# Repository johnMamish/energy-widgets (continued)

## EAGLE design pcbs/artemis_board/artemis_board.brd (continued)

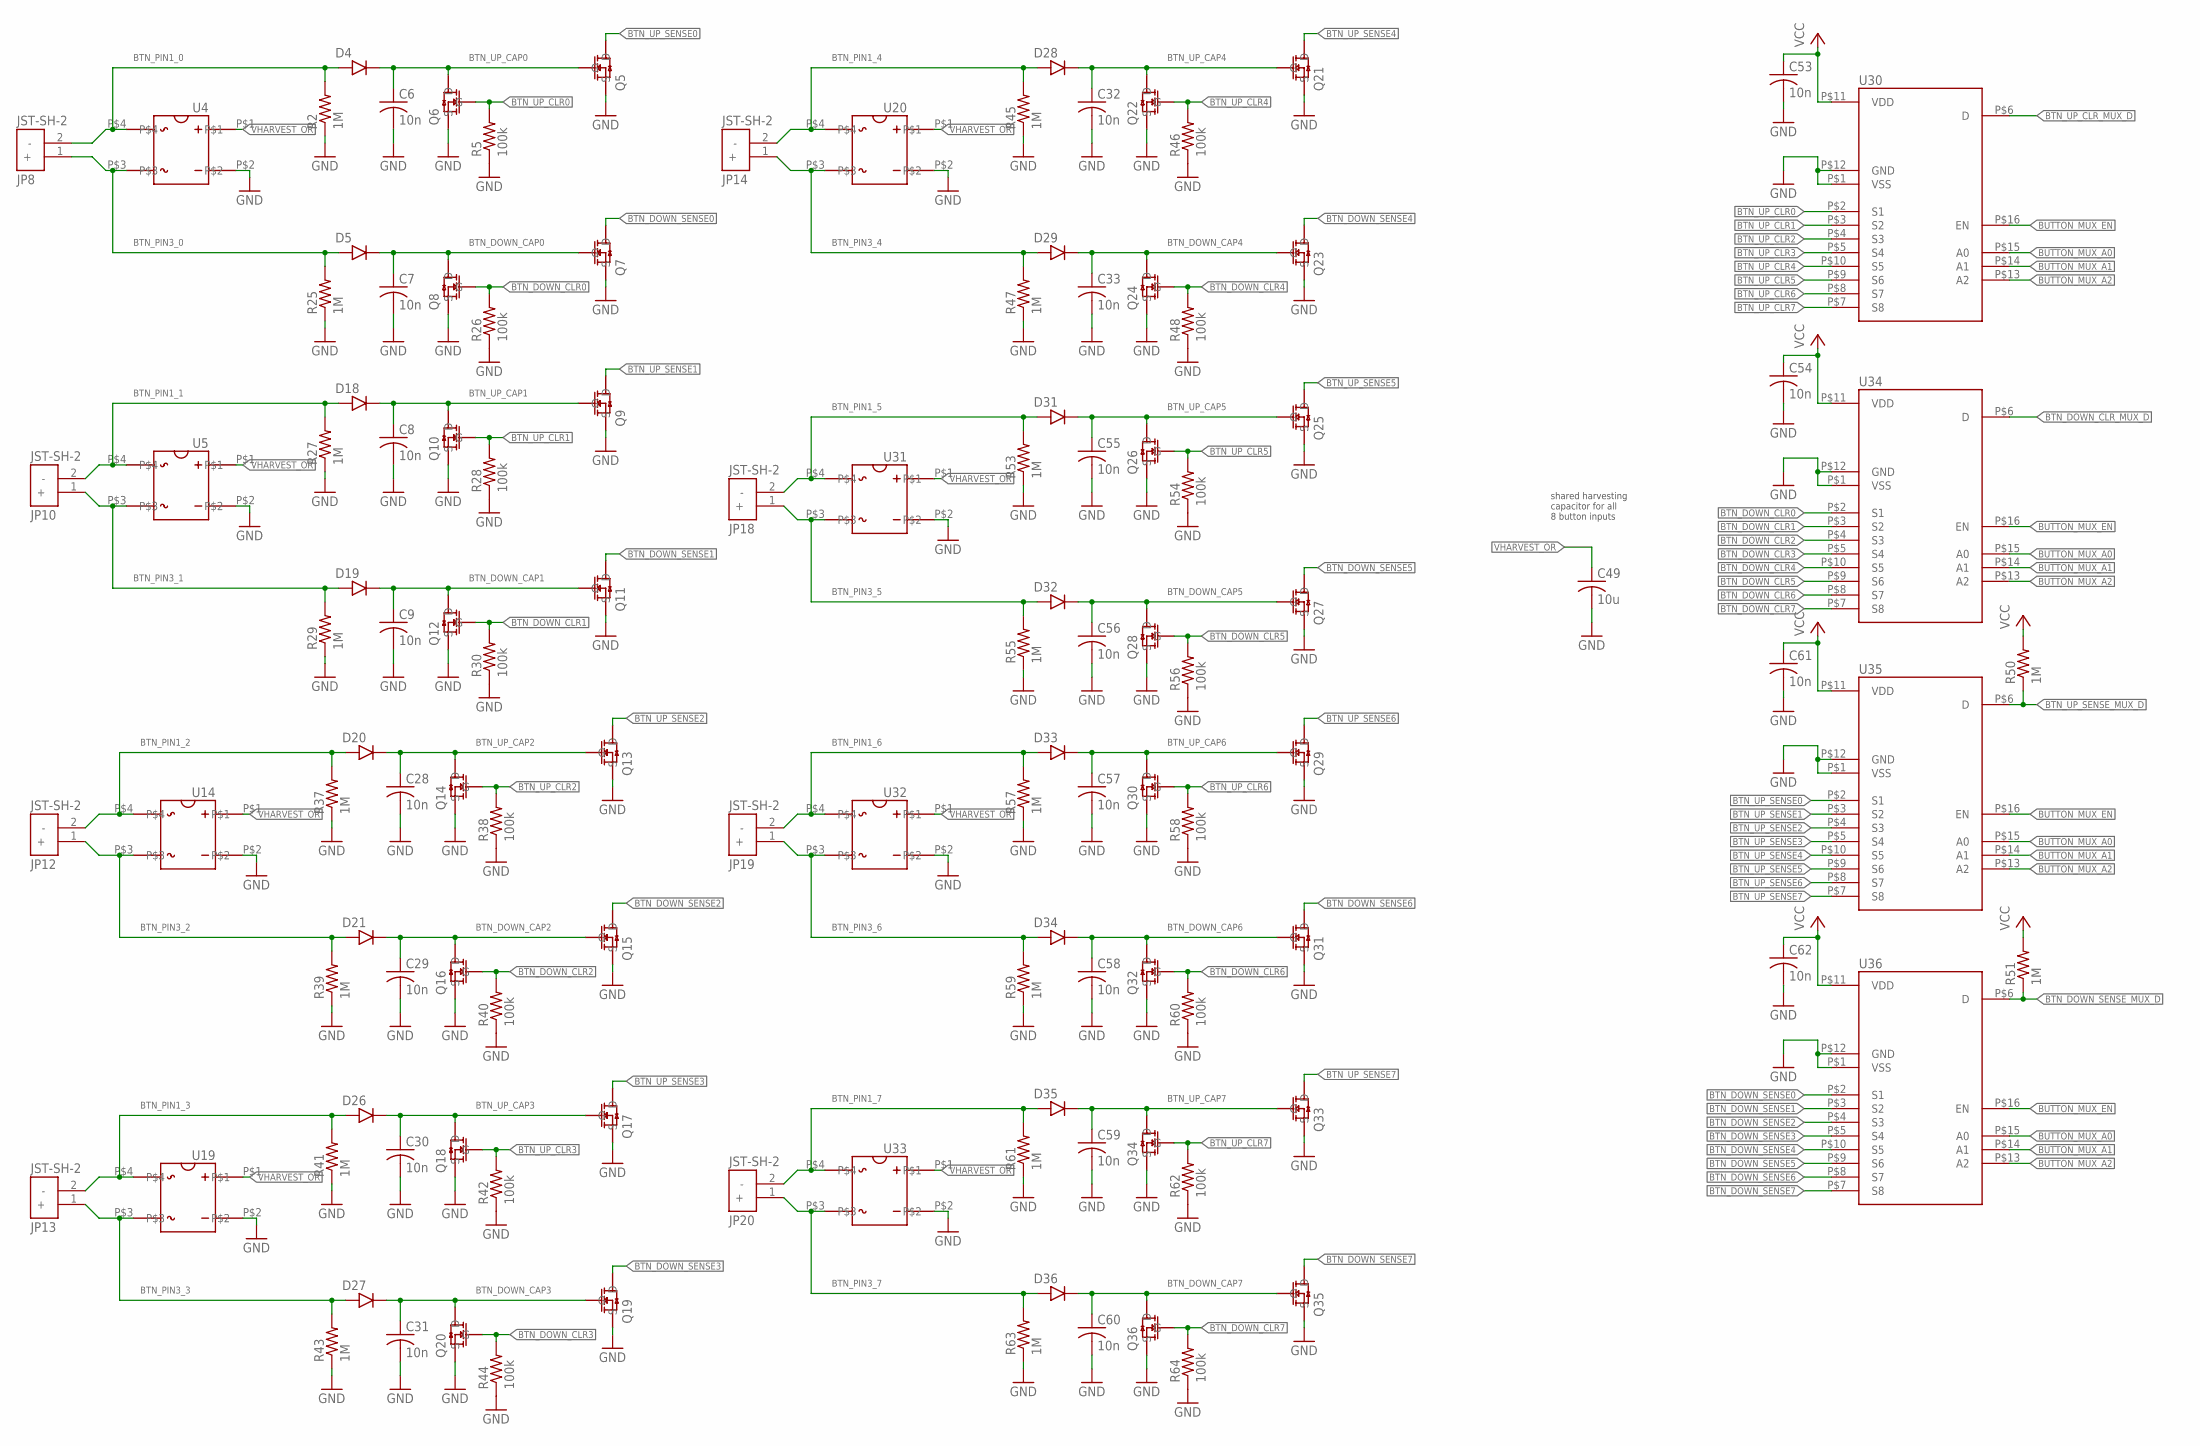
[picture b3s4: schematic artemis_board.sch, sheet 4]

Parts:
C6, C7, C8, C9, C28, C29, C30, C31, C32, C33, C53, C54, C55, C56, C57, C58, C59, C60, C61, C62: 10n; C0402; MFR_PN CL05B103KO5NNNC
C49: 10u; C0603; MFR_PN CL10A106MQ8NNNC
D4, D5, D18, D19, D20, D21, D26, D27, D28, D29, D31, D32, D33, D34, D35, D36: DFLU1200; MFR_PN DFLU1200-7
JP8, JP10, JP12, JP13, JP14, JP18, JP19, JP20: JST-SH-2; MFR_PN SM02B-SRSS-TB(LF)(SN)
Q5, Q7, Q9, Q11, Q13, Q15, Q17, Q19, Q21, Q23, Q25, Q27, Q29, Q31, Q33, Q35: 2N7002K-7
Q6, Q8, Q10, Q12, Q14, Q16, Q18, Q20, Q22, Q24, Q26, Q28, Q30, Q32, Q34, Q36: BSS138K
R2, R25, R27, R29, R37, R39, R41, R43, R45, R47, R50, R51, R53, R55, R57, R59, R61, R63: 1M; R0402; MFR_PN RC0402FR-071ML
R5, R26, R28, R30, R38, R40, R42, R44, R46, R48, R54, R56, R58, R60, R62, R64: 100k; R0402; MFR_PN RC0402FR-07100KL
U4, U5, U14, U19, U20, U31, U32, U33: CDBHD140L-G; CDBHDXX0L-G; MFR_PN CDBHD140L-G
U30, U34, U35, U36: TMUX1108RSVR; UQFN16-RSV0016A

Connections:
BTN_DOWN_CAP0: C7.1, D5.K, Q7.G, Q8.D
BTN_DOWN_CAP1: C9.1, D19.K, Q11.G, Q12.D
BTN_DOWN_CAP2: C29.1, D21.K, Q15.G, Q16.D
BTN_DOWN_CAP3: C31.1, D27.K, Q19.G, Q20.D
BTN_DOWN_CAP4: C33.1, D29.K, Q23.G, Q24.D
BTN_DOWN_CAP5: C56.1, D32.K, Q27.G, Q28.D
BTN_DOWN_CAP6: C58.1, D34.K, Q31.G, Q32.D
BTN_DOWN_CAP7: C60.1, D36.K, Q35.G, Q36.D
BTN_DOWN_CLR0: Q8.G, R26.2, U34.P$2 (S1)
BTN_DOWN_CLR1: Q12.G, R30.2, U34.P$3 (S2)
BTN_DOWN_CLR2: Q16.G, R40.2, U34.P$4 (S3)
BTN_DOWN_CLR3: Q20.G, R44.2, U34.P$5 (S4)
BTN_DOWN_CLR4: Q24.G, R48.2, U34.P$10 (S5)
BTN_DOWN_CLR5: Q28.G, R56.2, U34.P$9 (S6)
BTN_DOWN_CLR6: Q32.G, R60.2, U34.P$8 (S7)
BTN_DOWN_CLR7: Q36.G, R64.2, U34.P$7 (S8)
BTN_DOWN_CLR_MUX_D: U34.P$6 (D); also elsewhere on the board
BTN_DOWN_SENSE0: Q7.D, U36.P$2 (S1)
BTN_DOWN_SENSE1: Q11.D, U36.P$3 (S2)
BTN_DOWN_SENSE2: Q15.D, U36.P$4 (S3)
BTN_DOWN_SENSE3: Q19.D, U36.P$5 (S4)
BTN_DOWN_SENSE4: Q23.D, U36.P$10 (S5)
BTN_DOWN_SENSE5: Q27.D, U36.P$9 (S6)
BTN_DOWN_SENSE6: Q31.D, U36.P$8 (S7)
BTN_DOWN_SENSE7: Q35.D, U36.P$7 (S8)
BTN_DOWN_SENSE_MUX_D: R51.1, U36.P$6 (D); also elsewhere on the board
BTN_PIN1_0: D4.A, JP8.2 (-), R2.2, U4.P$4
BTN_PIN1_1: D18.A, JP10.2 (-), R27.2, U5.P$4
BTN_PIN1_2: D20.A, JP12.2 (-), R37.2, U14.P$4
BTN_PIN1_3: D26.A, JP13.2 (-), R41.2, U19.P$4
BTN_PIN1_4: D28.A, JP14.2 (-), R45.2, U20.P$4
BTN_PIN1_5: D31.A, JP18.2 (-), R53.2, U31.P$4
BTN_PIN1_6: D33.A, JP19.2 (-), R57.2, U32.P$4
BTN_PIN1_7: D35.A, JP20.2 (-), R61.2, U33.P$4
BTN_PIN3_0: D5.A, JP8.1 (+), R25.2, U4.P$3
BTN_PIN3_1: D19.A, JP10.1 (+), R29.2, U5.P$3
BTN_PIN3_2: D21.A, JP12.1 (+), R39.2, U14.P$3
BTN_PIN3_3: D27.A, JP13.1 (+), R43.2, U19.P$3
BTN_PIN3_4: D29.A, JP14.1 (+), R47.2, U20.P$3
BTN_PIN3_5: D32.A, JP18.1 (+), R55.2, U31.P$3
BTN_PIN3_6: D34.A, JP19.1 (+), R59.2, U32.P$3
BTN_PIN3_7: D36.A, JP20.1 (+), R63.2, U33.P$3
BTN_UP_CAP0: C6.1, D4.K, Q5.G, Q6.D
BTN_UP_CAP1: C8.1, D18.K, Q9.G, Q10.D
BTN_UP_CAP2: C28.1, D20.K, Q13.G, Q14.D
BTN_UP_CAP3: C30.1, D26.K, Q17.G, Q18.D
BTN_UP_CAP4: C32.1, D28.K, Q21.G, Q22.D
BTN_UP_CAP5: C55.1, D31.K, Q25.G, Q26.D
BTN_UP_CAP6: C57.1, D33.K, Q29.G, Q30.D
BTN_UP_CAP7: C59.1, D35.K, Q33.G, Q34.D
BTN_UP_CLR0: Q6.G, R5.2, U30.P$2 (S1)
BTN_UP_CLR1: Q10.G, R28.2, U30.P$3 (S2)
BTN_UP_CLR2: Q14.G, R38.2, U30.P$4 (S3)
BTN_UP_CLR3: Q18.G, R42.2, U30.P$5 (S4)
BTN_UP_CLR4: Q22.G, R46.2, U30.P$10 (S5)
BTN_UP_CLR5: Q26.G, R54.2, U30.P$9 (S6)
BTN_UP_CLR6: Q30.G, R58.2, U30.P$8 (S7)
BTN_UP_CLR7: Q34.G, R62.2, U30.P$7 (S8)
BTN_UP_CLR_MUX_D: U30.P$6 (D); also elsewhere on the board
BTN_UP_SENSE0: Q5.D, U35.P$2 (S1)
BTN_UP_SENSE1: Q9.D, U35.P$3 (S2)
BTN_UP_SENSE2: Q13.D, U35.P$4 (S3)
BTN_UP_SENSE3: Q17.D, U35.P$5 (S4)
BTN_UP_SENSE4: Q21.D, U35.P$10 (S5)
BTN_UP_SENSE5: Q25.D, U35.P$9 (S6)
BTN_UP_SENSE6: Q29.D, U35.P$8 (S7)
BTN_UP_SENSE7: Q33.D, U35.P$7 (S8)
BTN_UP_SENSE_MUX_D: R50.1, U35.P$6 (D); also elsewhere on the board
BUTTON_MUX_A0: U30.P$15 (A0), U34.P$15 (A0), U35.P$15 (A0), U36.P$15 (A0); also elsewhere on the board
BUTTON_MUX_A1: U30.P$14 (A1), U34.P$14 (A1), U35.P$14 (A1), U36.P$14 (A1); also elsewhere on the board
BUTTON_MUX_A2: U30.P$13 (A2), U34.P$13 (A2), U35.P$13 (A2), U36.P$13 (A2); also elsewhere on the board
BUTTON_MUX_EN: U30.P$16 (EN), U34.P$16 (EN), U35.P$16 (EN), U36.P$16 (EN); also elsewhere on the board
GND: C6.2, C7.2, C8.2, C9.2, C28.2, C29.2, C30.2, C31.2, C32.2, C33.2, C49.2, C53.2, C54.2, C55.2, C56.2, C57.2, C58.2, C59.2, C60.2, C61.2, C62.2, Q5.S, Q6.S, Q7.S, Q8.S, Q9.S, Q10.S, Q11.S, Q12.S, Q13.S, Q14.S, Q15.S, Q16.S, Q17.S, Q18.S, Q19.S, Q20.S, Q21.S, Q22.S, Q23.S, Q24.S, Q25.S, Q26.S, Q27.S, Q28.S, Q29.S, Q30.S, Q31.S, Q32.S, Q33.S, Q34.S, Q35.S, Q36.S, R2.1, R5.1, R25.1, R26.1, R27.1, R28.1, R29.1, R30.1, R37.1, R38.1, R39.1, R40.1, R41.1, R42.1, R43.1, R44.1, R45.1, R46.1, R47.1, R48.1, R53.1, R54.1, R55.1, R56.1, R57.1, R58.1, R59.1, R60.1, R61.1, R62.1, R63.1, R64.1, U4.P$2, U5.P$2, U14.P$2, U19.P$2, U20.P$2, U30.P$1 (VSS), U30.P$12 (GND), U31.P$2, U32.P$2, U33.P$2, U34.P$1 (VSS), U34.P$12 (GND), U35.P$1 (VSS), U35.P$12 (GND), U36.P$1 (VSS), U36.P$12 (GND); also elsewhere on the board
VCC: C53.1, C54.1, C61.1, C62.1, R50.2, R51.2, U30.P$11 (VDD), U34.P$11 (VDD), U35.P$11 (VDD), U36.P$11 (VDD); also elsewhere on the board
VHARVEST_OR: C49.1, U4.P$1, U5.P$1, U14.P$1, U19.P$1, U20.P$1, U31.P$1, U32.P$1, U33.P$1; also elsewhere on the board

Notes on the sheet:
shared harvesting capacitor for all 8 button inputs

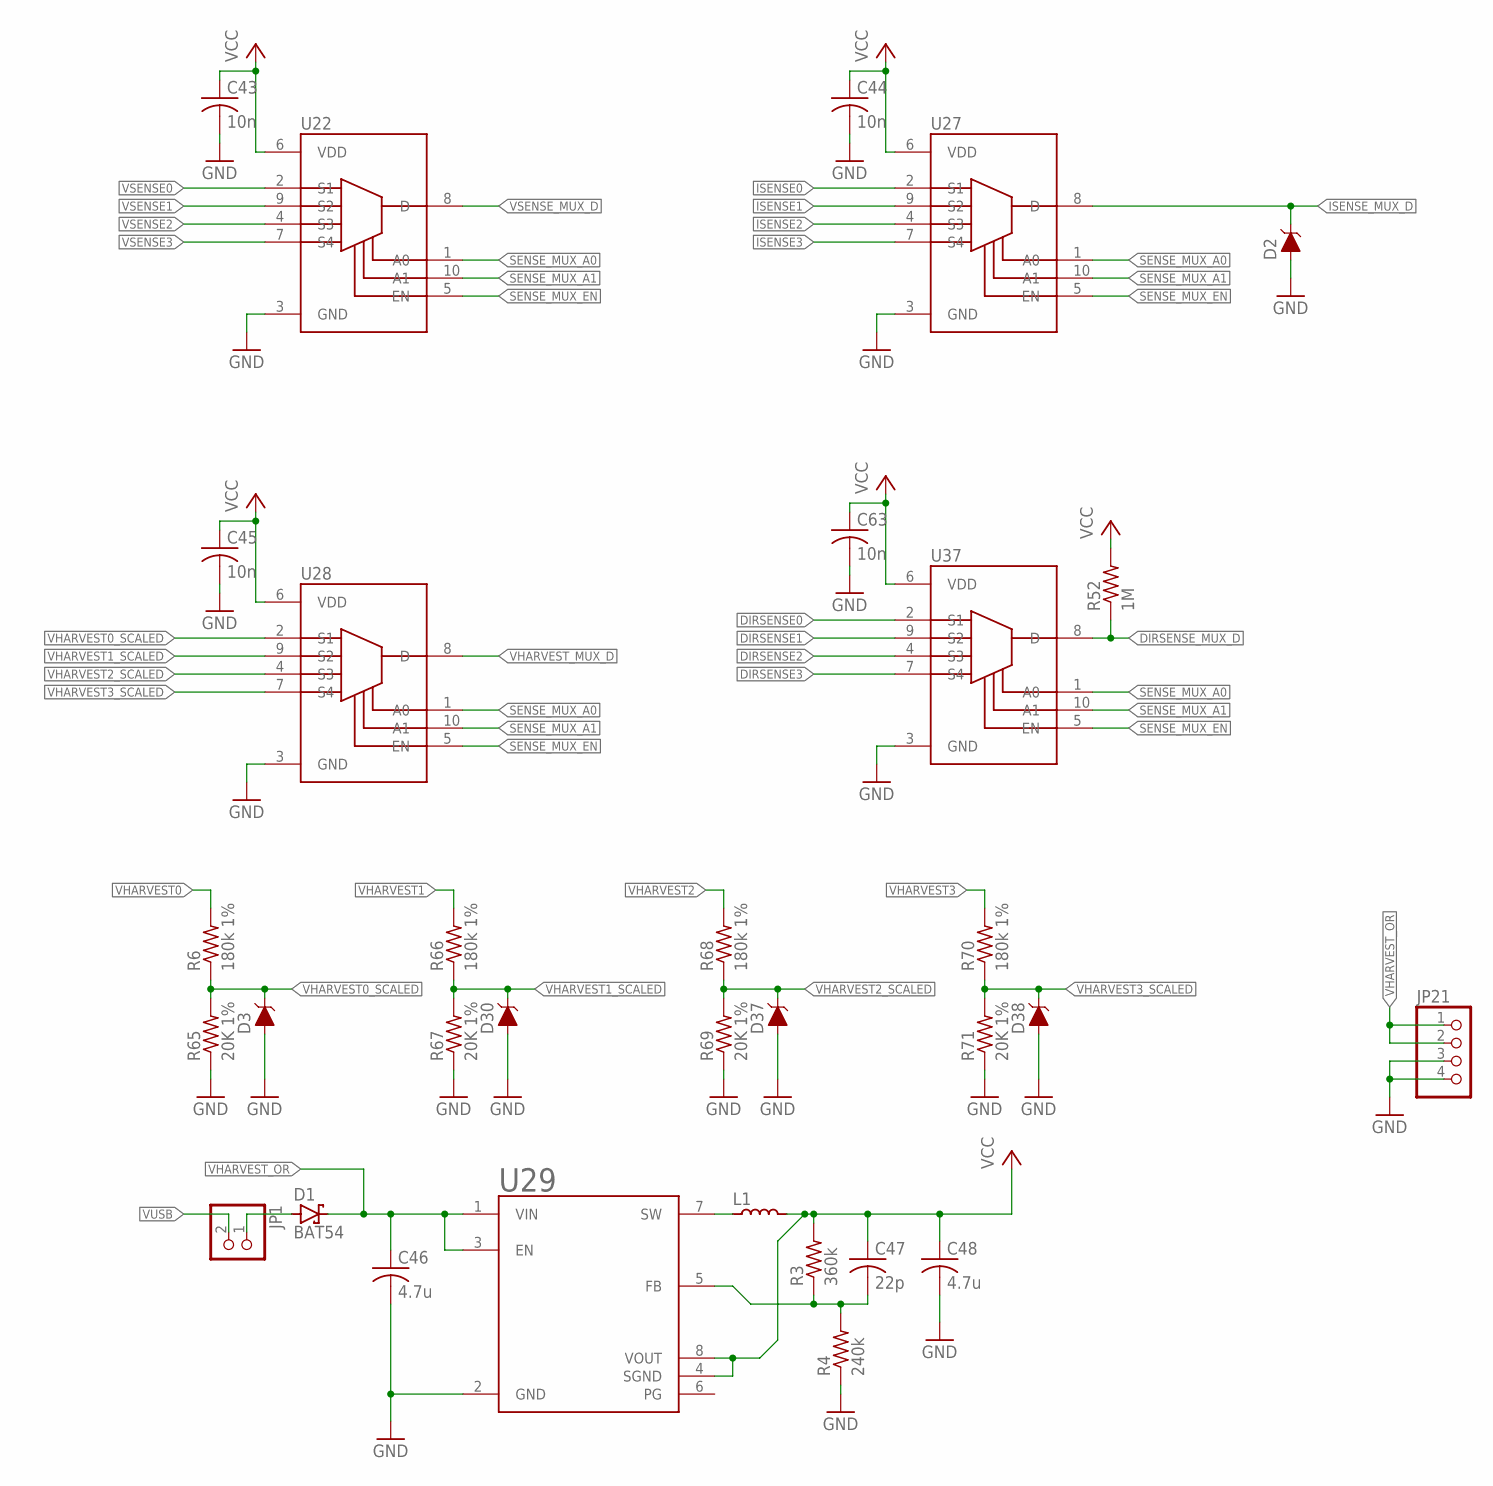
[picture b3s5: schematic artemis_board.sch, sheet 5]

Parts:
C43, C44, C45, C63: 10n; C0402; MFR_PN CL05B103KO5NNNC
C46, C48: 4.7u; C0603; MFR_PN CL10A475KA8NQNC
C47: 22p; C0402; MFR_PN C0603C220J5GACTU
D1: BAT54; SOT23; MFR_PN BAT54
D2, D3, D30, D37, D38: 3.3V; SOD-323; MFR_PN BZT52C2V0S-7-F
JP1: PINHD-1X2; 1X02
JP21: PINHD-1X4; 1X04
L1: 22u; LQH3NPNXXXXMEX; MFR_PN LQH3NPN220MJRL
R3: 360k; R0603; MFR_PN ERJ-3GEYJ364V
R4: 240k; R0603; MFR_PN ERJ-3GEYJ244V
R6, R66, R68, R70: 180k 1%; R0402; MFR_PN ERJ-2RKF1803X
R52: 1M; R0402; MFR_PN RC0402FR-071ML
R65, R67, R69, R71: 20K 1%; R0402; MFR_PN ERJ-2RKF2002X
U22, U27, U28, U37: TMUX1104DGSR; SOP50P490X110-10N
U29: TPS62120; SOP65P280X145-8N; MFR_PN TPS62120

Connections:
DIRSENSE0: U37.2 (S1); also elsewhere on the board
DIRSENSE1: U37.9 (S2); also elsewhere on the board
DIRSENSE2: U37.4 (S3); also elsewhere on the board
DIRSENSE3: U37.7 (S4); also elsewhere on the board
DIRSENSE_MUX_D: R52.1, U37.8 (D); also elsewhere on the board
GND: C43.2, C44.2, C45.2, C46.2, C48.2, C63.2, D2.A, D3.A, D30.A, D37.A, D38.A, JP21.3, JP21.4, R4.1, R65.1, R67.1, R69.1, R71.1, U22.3 (GND), U27.3 (GND), U28.3 (GND), U29.2 (GND), U37.3 (GND); also elsewhere on the board
ISENSE0: U27.2 (S1); also elsewhere on the board
ISENSE1: U27.9 (S2); also elsewhere on the board
ISENSE2: U27.4 (S3); also elsewhere on the board
ISENSE3: U27.7 (S4); also elsewhere on the board
ISENSE_MUX_D: D2.C, U27.8 (D); also elsewhere on the board
unnamed: D1.1 (A), JP1.1
unnamed: C47.2, R3.1, R4.2, U29.5 (FB)
unnamed: L1.P$1, U29.7 (SW)
SENSE_MUX_A0: U22.1 (A0), U27.1 (A0), U28.1 (A0), U37.1 (A0); also elsewhere on the board
SENSE_MUX_A1: U22.10 (A1), U27.10 (A1), U28.10 (A1), U37.10 (A1); also elsewhere on the board
SENSE_MUX_EN: U22.5 (EN), U27.5 (EN), U28.5 (EN), U37.5 (EN); also elsewhere on the board
VCC: C43.1, C44.1, C45.1, C47.1, C48.1, C63.1, L1.P$2, R3.2, R52.2, U22.6 (VDD), U27.6 (VDD), U28.6 (VDD), U29.4 (SGND), U29.8 (VOUT), U37.6 (VDD); also elsewhere on the board
VHARVEST0: R6.2; also elsewhere on the board
VHARVEST0_SCALED: D3.C, R6.1, R65.2, U28.2 (S1)
VHARVEST1: R66.2; also elsewhere on the board
VHARVEST1_SCALED: D30.C, R66.1, R67.2, U28.9 (S2)
VHARVEST2: R68.2; also elsewhere on the board
VHARVEST2_SCALED: D37.C, R68.1, R69.2, U28.4 (S3)
VHARVEST3: R70.2; also elsewhere on the board
VHARVEST3_SCALED: D38.C, R70.1, R71.2, U28.7 (S4)
VHARVEST_MUX_D: U28.8 (D); also elsewhere on the board
VHARVEST_OR: C46.1, D1.3 (C), JP21.1, JP21.2, U29.1 (VIN), U29.3 (EN); also elsewhere on the board
VSENSE0: U22.2 (S1); also elsewhere on the board
VSENSE1: U22.9 (S2); also elsewhere on the board
VSENSE2: U22.4 (S3); also elsewhere on the board
VSENSE3: U22.7 (S4); also elsewhere on the board
VSENSE_MUX_D: U22.8 (D); also elsewhere on the board
VUSB: JP1.2; also elsewhere on the board

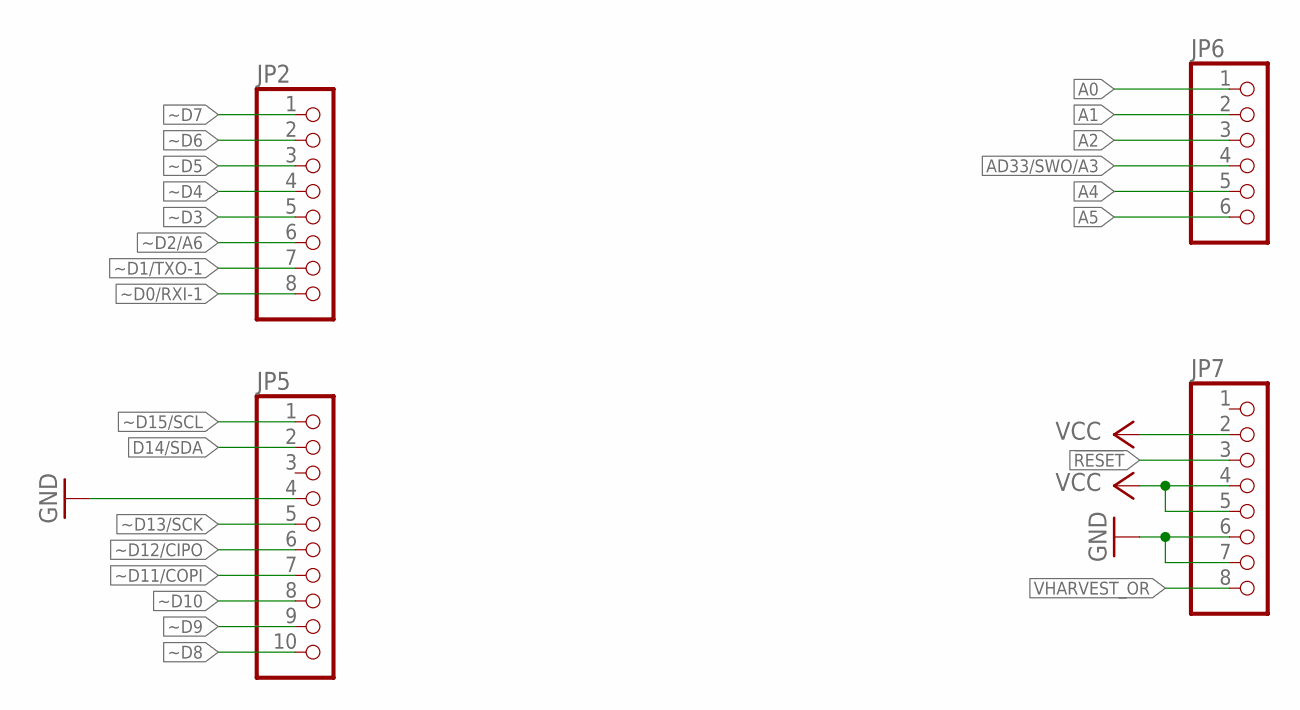
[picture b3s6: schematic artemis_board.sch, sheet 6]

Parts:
JP2, JP7: PINHD-1X8; 1X08
JP5: PINHD-1X10; 1X10
JP6: PINHD-1X6; 1X06

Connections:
!RESET: JP7.3; also elsewhere on the board
A0: JP6.1; also elsewhere on the board
A1: JP6.2; also elsewhere on the board
A2: JP6.3; also elsewhere on the board
A4: JP6.5; also elsewhere on the board
A5: JP6.6; also elsewhere on the board
AD33/SWO/A3: JP6.4; also elsewhere on the board
D14/SDA: JP5.2; also elsewhere on the board
GND: JP5.4, JP7.6, JP7.7; also elsewhere on the board
VCC: JP7.2, JP7.4, JP7.5; also elsewhere on the board
VHARVEST_OR: JP7.8; also elsewhere on the board
~D0/RXI-1: JP2.8; also elsewhere on the board
~D1/TXO-1: JP2.7; also elsewhere on the board
~D2/A6: JP2.6; also elsewhere on the board
~D3: JP2.5; also elsewhere on the board
~D4: JP2.4; also elsewhere on the board
~D5: JP2.3; also elsewhere on the board
~D6: JP2.2; also elsewhere on the board
~D7: JP2.1; also elsewhere on the board
~D8: JP5.10; also elsewhere on the board
~D9: JP5.9; also elsewhere on the board
~D10: JP5.8; also elsewhere on the board
~D11/COPI: JP5.7; also elsewhere on the board
~D12/CIPO: JP5.6; also elsewhere on the board
~D13/SCK: JP5.5; also elsewhere on the board
~D15/SCL: JP5.1; also elsewhere on the board

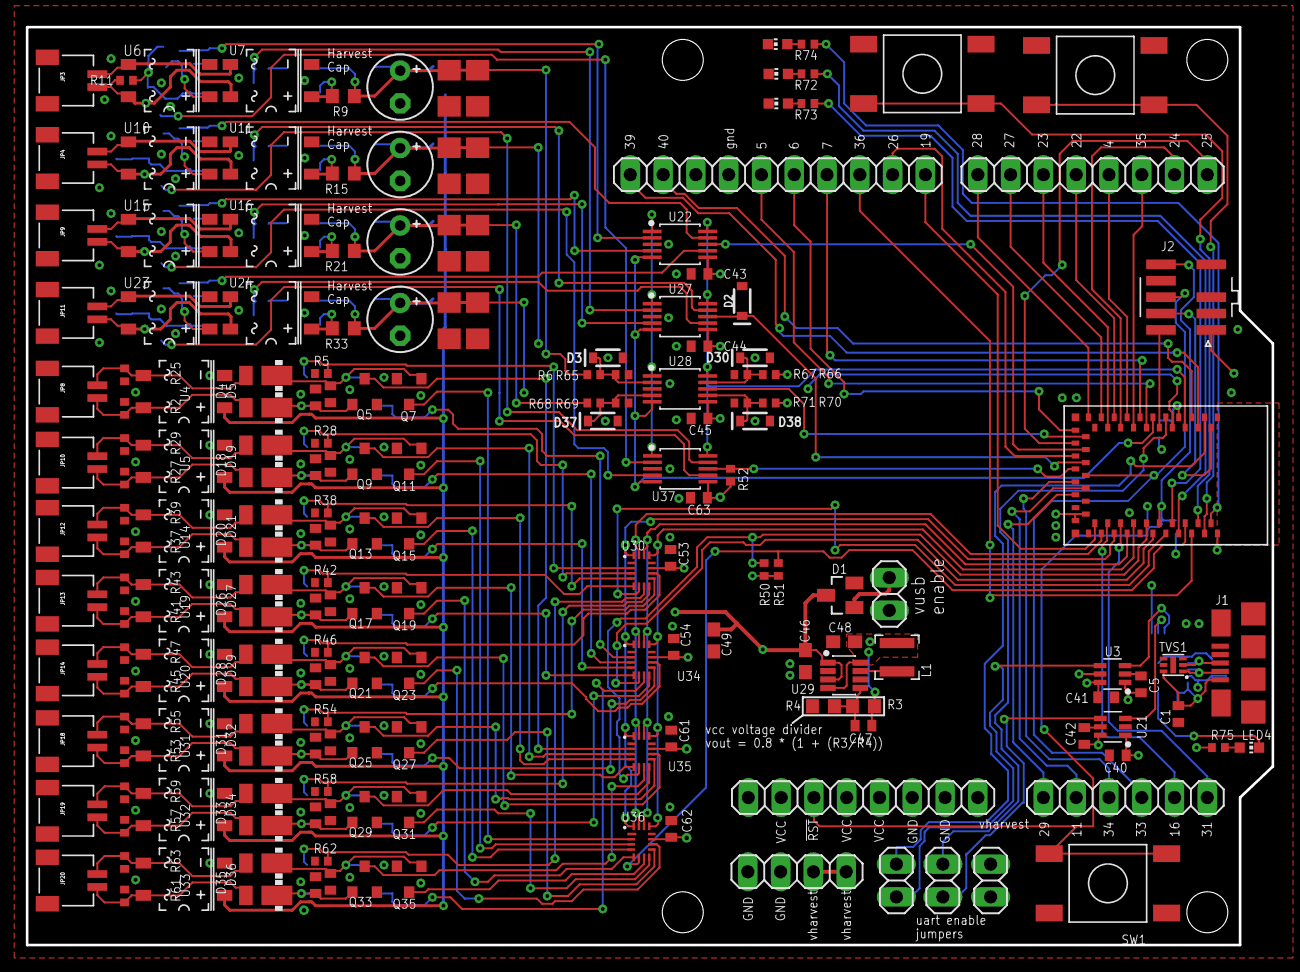
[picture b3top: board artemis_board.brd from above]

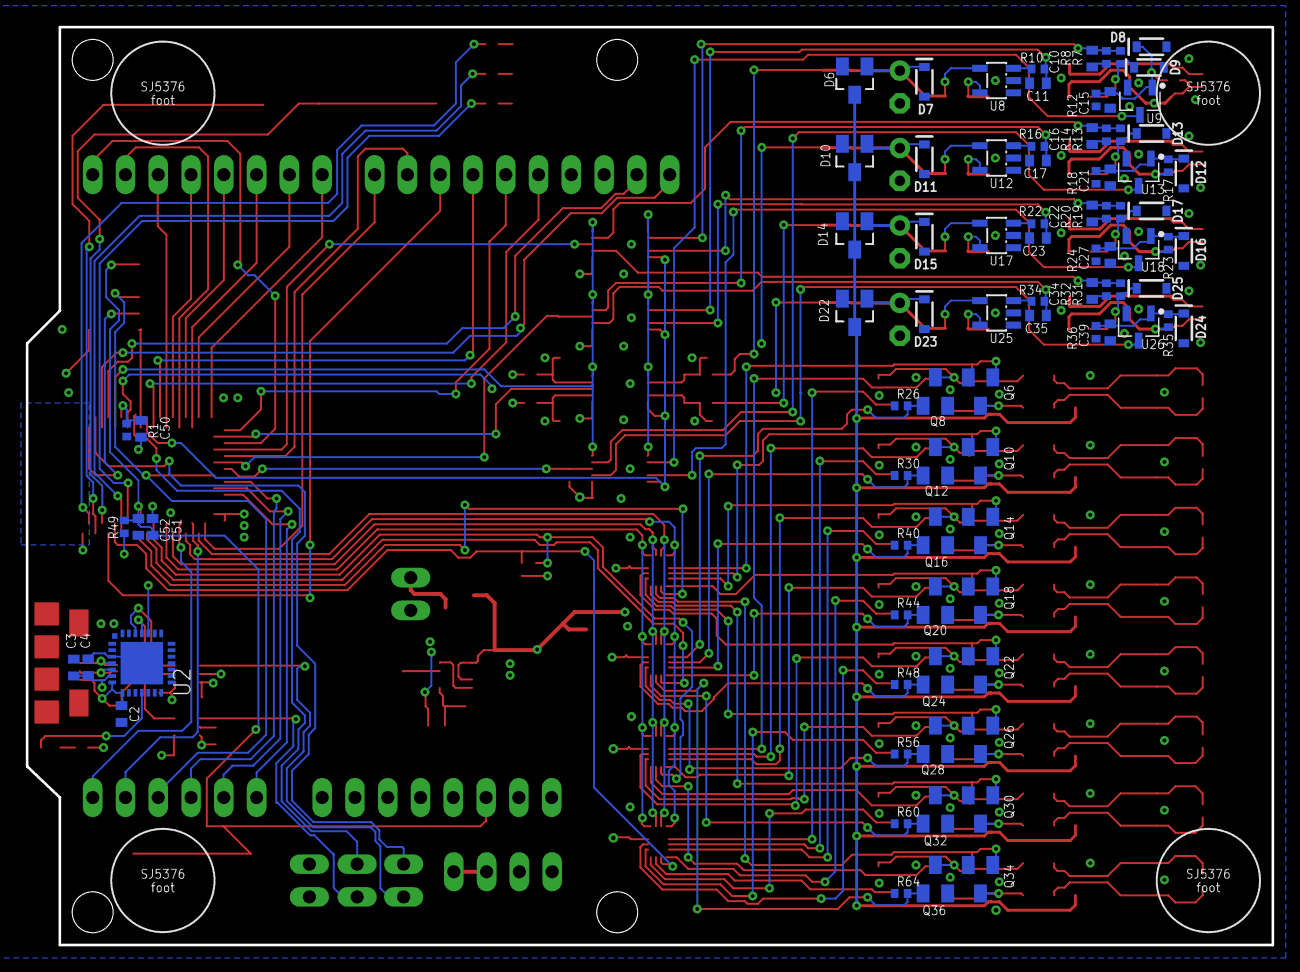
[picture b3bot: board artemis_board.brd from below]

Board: 4 copper layers, 96.5 x 71.1 mm, 277 parts (88 on the bottom side), 177 nets.

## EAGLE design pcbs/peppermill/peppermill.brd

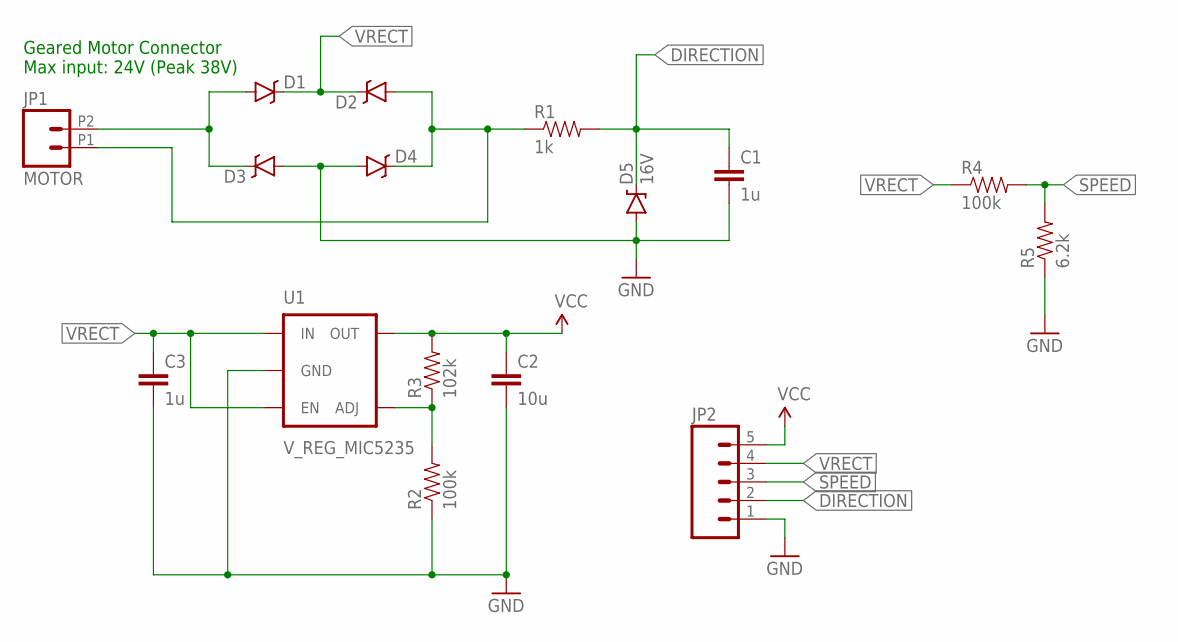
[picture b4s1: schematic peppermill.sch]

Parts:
C1, C3: 1u; 0805
C2: 10u; 0805
D1, D2, D3, D4: BAT20JFILM; SOD-323; DIGIKEY 1727-3877-1-ND
D5: 16V; SOD-123; DIGIKEY 1727-3600-1-ND
JP1: MOTOR; 1X02_2.54_SCREWTERM
JP2: M05LOCK; 1X05_LOCK
R1: 1k; 0805
R2, R4: 100k; 0805
R3: 102k; 0805
R5: 6.2k; 0805
U1: V_REG_MIC5235; SOT23-5; DIGIKEY 576-1284-1-ND

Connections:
DIRECTION: C1.1, D5.C, JP2.2, R1.2
GND: C1.2, C2.2, C3.2, D3.A, D4.A, D5.A, JP2.1, R2.1, R5.1, U1.2 (GND)
unnamed: R2.2, R3.1, U1.4 (ADJ)
unnamed: D1.A, D3.C, JP1.P2 (2)
unnamed: D2.A, D4.C, JP1.P1 (1), R1.1
SPEED: JP2.3, R4.2, R5.2
VCC: C2.1, JP2.5, R3.2, U1.5 (OUT)
VRECT: C3.1, D1.C, D2.C, JP2.4, R4.1, U1.1 (IN), U1.3 (EN)

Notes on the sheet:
Geared Motor Connector Max input: 24V (Peak 38V)

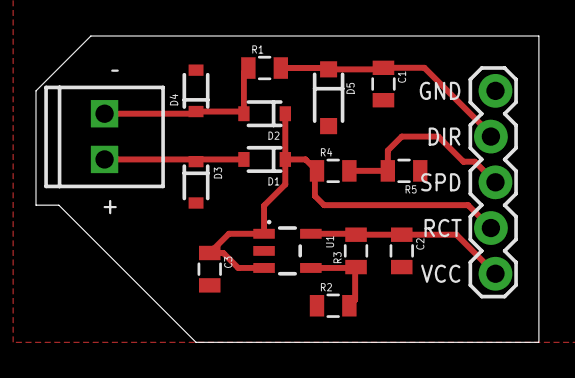
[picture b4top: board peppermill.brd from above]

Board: 2 copper layers, 27.9 x 17.0 mm, 16 parts (0 on the bottom side), 8 nets.

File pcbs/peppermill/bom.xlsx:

Part | Value | Device | Package | Description | DIGIKEY | PROD_ID | VALUE
C1 | 1u | CAP0805 | 805 | Capacitor
C2 | 10u | CAP0805 | 805 | Capacitor
C3 | 1u | CAP0805 | 805 | Capacitor
D1 |  | BAT20JFILM | SOD-323 | 23V, 1A Schottky diode, SOD-323 package | 1727-3877-1-ND | DIO-11623 | BAT20JFILM
D2 |  | BAT20JFILM | SOD-323 | 23V, 1A Schottky diode, SOD-323 package | 1727-3877-1-ND | DIO-11623 | BAT20JFILM
D3 |  | BAT20JFILM | SOD-323 | 23V, 1A Schottky diode, SOD-323 package | 1727-3877-1-ND | DIO-11623 | BAT20JFILM
D4 |  | BAT20JFILM | SOD-323 | 23V, 1A Schottky diode, SOD-323 package | 1727-3877-1-ND | DIO-11623 | BAT20JFILM
D5 | 16V | DIODE-ZENER16V | SOD-123 | Zener Diode | 1727-3600-1-ND | DIO-12440 | 16V
JP1 | MOTOR | M022.54MM_SCREWTERM | 1X02_2.54_SCREWTERM | Standard 2-pin 0.1 header. Use with"
JP2 |  | M05LOCK | 1X05_LOCK | Header 5
R1 | 1k | RESISTOR0805-RES | 805 | Resistor
R2 | 100k | RESISTOR0805-RES | 805 | Resistor
R3 | 102k | RESISTOR0805-RES | 805 | Resistor
R4 | 100k | RESISTOR0805-RES | 805 | Resistor
R5 | 6.2k | RESISTOR0805-RES | 805 | Resistor
U1 | V_REG_MIC5235 | V_REG_MIC5235 | SOT23-5 |  | 576-1284-1-ND

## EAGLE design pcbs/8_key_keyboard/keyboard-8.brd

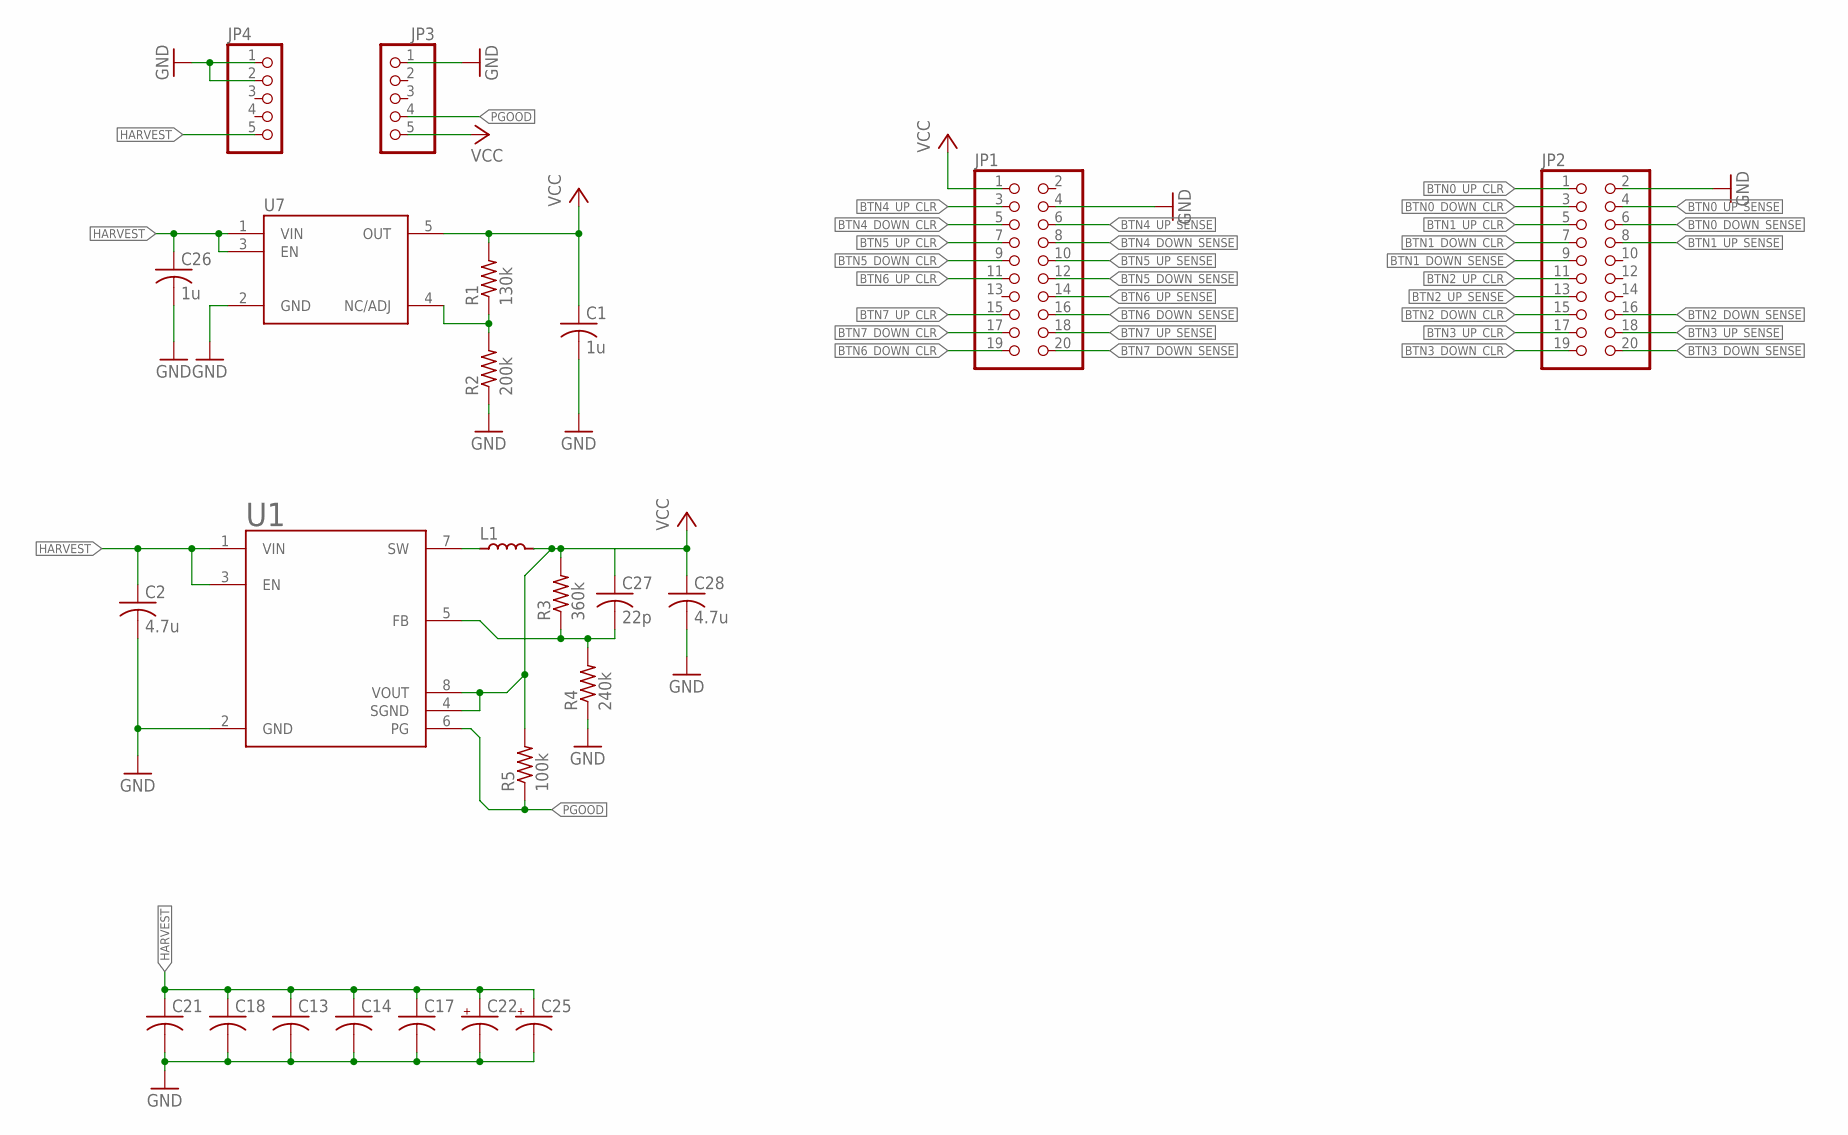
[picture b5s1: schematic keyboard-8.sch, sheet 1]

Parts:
C1, C26: 1u; C0402
C2, C28: 4.7u; C0603
C13, C14, C17: C-USC1206; C1206
C18, C21: C-USC0805; C0805
C22, C25: CPOL-USE2-5; E2-5
C27: 22p; C0402
JP1, JP2: PINHD-2X10; 2X10
JP3, JP4: PINHD-1X5; 1X05
L1: 22u; LQH3NPNXXXXMEX
R1: 130k; R0603
R2: 200k; R0603
R3: 360k; R0402
R4: 240k; R0402
R5: 100k; R0402
U1: TPS62120; SOP65P280X145-8N
U7: MIC5225

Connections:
BTN0_DOWN_CLR: JP2.3; also elsewhere on the board
BTN0_DOWN_SENSE: JP2.6; also elsewhere on the board
BTN0_UP_CLR: JP2.1; also elsewhere on the board
BTN0_UP_SENSE: JP2.4; also elsewhere on the board
BTN1_DOWN_CLR: JP2.7; also elsewhere on the board
BTN1_DOWN_SENSE: JP2.9; also elsewhere on the board
BTN1_UP_CLR: JP2.5; also elsewhere on the board
BTN1_UP_SENSE: JP2.8; also elsewhere on the board
BTN2_DOWN_CLR: JP2.15; also elsewhere on the board
BTN2_DOWN_SENSE: JP2.16; also elsewhere on the board
BTN2_UP_CLR: JP2.11; also elsewhere on the board
BTN2_UP_SENSE: JP2.13; also elsewhere on the board
BTN3_DOWN_CLR: JP2.19; also elsewhere on the board
BTN3_DOWN_SENSE: JP2.20; also elsewhere on the board
BTN3_UP_CLR: JP2.17; also elsewhere on the board
BTN3_UP_SENSE: JP2.18; also elsewhere on the board
BTN4_DOWN_CLR: JP1.5; also elsewhere on the board
BTN4_DOWN_SENSE: JP1.8; also elsewhere on the board
BTN4_UP_CLR: JP1.3; also elsewhere on the board
BTN4_UP_SENSE: JP1.6; also elsewhere on the board
BTN5_DOWN_CLR: JP1.9; also elsewhere on the board
BTN5_DOWN_SENSE: JP1.12; also elsewhere on the board
BTN5_UP_CLR: JP1.7; also elsewhere on the board
BTN5_UP_SENSE: JP1.10; also elsewhere on the board
BTN6_DOWN_CLR: JP1.19; also elsewhere on the board
BTN6_DOWN_SENSE: JP1.16; also elsewhere on the board
BTN6_UP_CLR: JP1.11; also elsewhere on the board
BTN6_UP_SENSE: JP1.14; also elsewhere on the board
BTN7_DOWN_CLR: JP1.17; also elsewhere on the board
BTN7_DOWN_SENSE: JP1.20; also elsewhere on the board
BTN7_UP_CLR: JP1.15; also elsewhere on the board
BTN7_UP_SENSE: JP1.18; also elsewhere on the board
GND: C1.2, C2.2, C13.2, C14.2, C17.2, C18.2, C21.2, C22.-, C25.-, C26.2, C28.2, JP1.4, JP2.2, JP3.1, JP4.1, JP4.2, R2.1, R4.1, U1.2 (GND), U7.2 (GND); also elsewhere on the board
HARVEST: C2.1, C13.1, C14.1, C17.1, C18.1, C21.1, C22.+, C25.+, C26.1, JP4.5, U1.1 (VIN), U1.3 (EN), U7.1 (VIN), U7.3 (EN); also elsewhere on the board
unnamed: R1.1, R2.2, U7.4 (NC/ADJ)
unnamed: C27.2, R3.1, R4.2, U1.5 (FB)
unnamed: L1.P$1, U1.7 (SW)
PGOOD: JP3.4, R5.1, U1.6 (PG)
VCC: C1.1, C27.1, C28.1, JP1.1, JP3.5, L1.P$2, R1.2, R3.2, R5.2, U1.4 (SGND), U1.8 (VOUT), U7.5 (OUT); also elsewhere on the board
